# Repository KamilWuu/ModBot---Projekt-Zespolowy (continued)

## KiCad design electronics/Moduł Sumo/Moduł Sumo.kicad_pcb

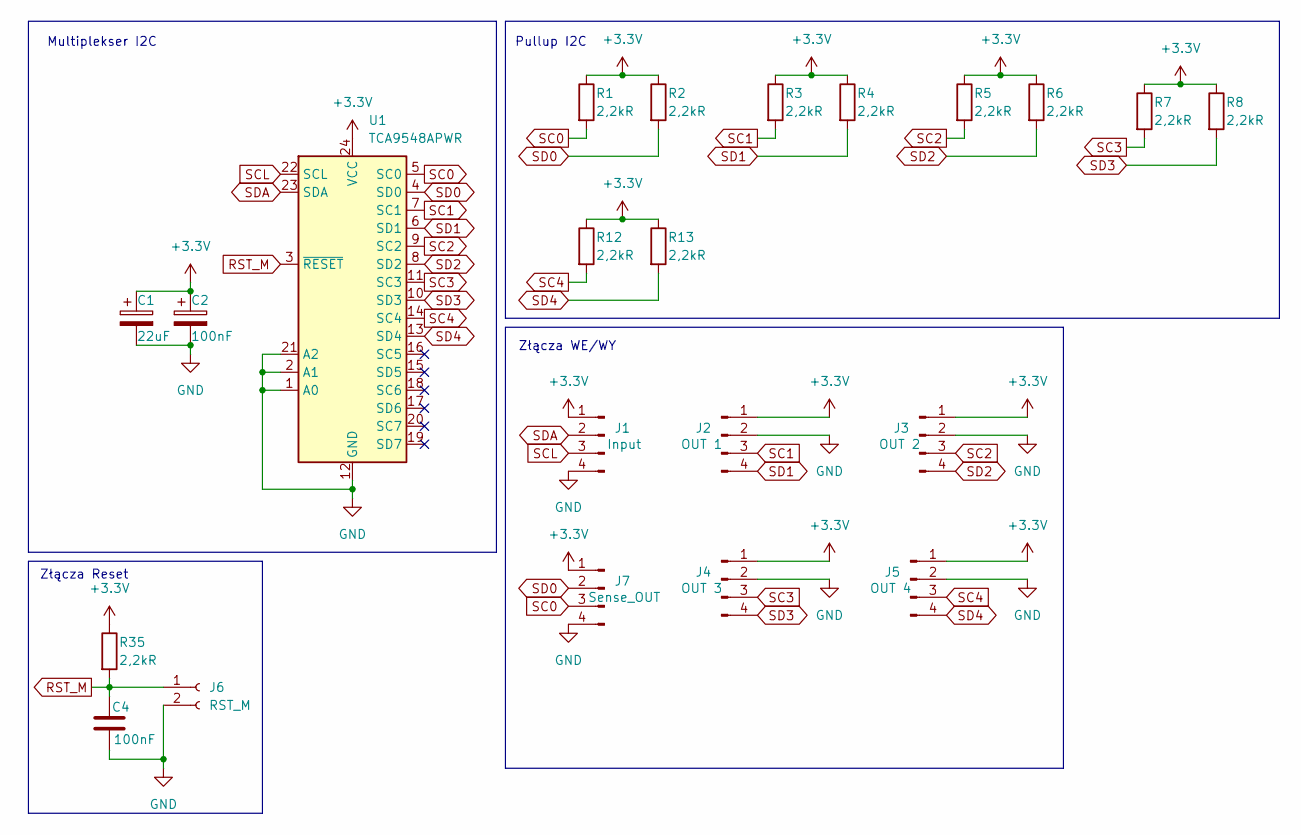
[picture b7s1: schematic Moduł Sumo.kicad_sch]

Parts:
C1: 22uF; C_0402_1005Metric_Pad0.74x0.62mm_HandSolder
C2, C4: 100nF; C_0402_1005Metric_Pad0.74x0.62mm_HandSolder
J1: Input; JST_EH_B4B-EH-A_1x04_P2.50mm_Vertical
J2: OUT 1; PinHeader_1x04_P2.54mm_Vertical
J3: OUT 2; PinHeader_1x04_P2.54mm_Vertical
J4: OUT 3; PinHeader_1x04_P2.54mm_Vertical
J5: OUT 4; PinHeader_1x04_P2.54mm_Vertical
J6: RST_M; PinSocket_1x02_P2.54mm_Vertical
J7: Sense_OUT; JST_EH_B4B-EH-A_1x04_P2.50mm_Vertical
R1, R2, R3, R4, R5, R6, R7, R8, R12, R13, R35: 2,2kR; R_0402_1005Metric_Pad0.72x0.64mm_HandSolder
U1: TCA9548APWR; TSSOP-24_4.4x7.8mm_P0.65mm

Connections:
+3.3V: C1.1, C2.1, J1.1, J2.1, J3.1, J4.1, J5.1, J7.1, R1.1, R2.1, R3.1, R4.1, R5.1, R6.1, R7.1, R8.1, R12.1, R13.1, R35.1, U1.24 (VCC)
GND: C1.2, C2.2, C4.2, J1.4, J2.2, J3.2, J4.2, J5.2, J6.2, J7.4, U1.1 (A0), U1.2 (A1), U1.12 (GND), U1.21 (A2)
RST_M: C4.1, J6.1, R35.2, U1.3 (~RESET)
SC0: J7.3, R1.2, U1.5 (SC0)
SC1: J2.3, R3.2, U1.7 (SC1)
SC2: J3.3, R5.2, U1.9 (SC2)
SC3: J4.3, R7.2, U1.11 (SC3)
SC4: J5.3, R12.2, U1.14 (SC4)
SCL: J1.3, U1.22 (SCL)
SD0: J7.2, R2.2, U1.4 (SD0)
SD1: J2.4, R4.2, U1.6 (SD1)
SD2: J3.4, R6.2, U1.8 (SD2)
SD3: J4.4, R8.2, U1.10 (SD3)
SD4: J5.4, R13.2, U1.13 (SD4)
SDA: J1.2, U1.23 (SDA)

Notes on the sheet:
Złącza Reset
Złącza WE/WY
Multiplekser I2C
Pullup I2C

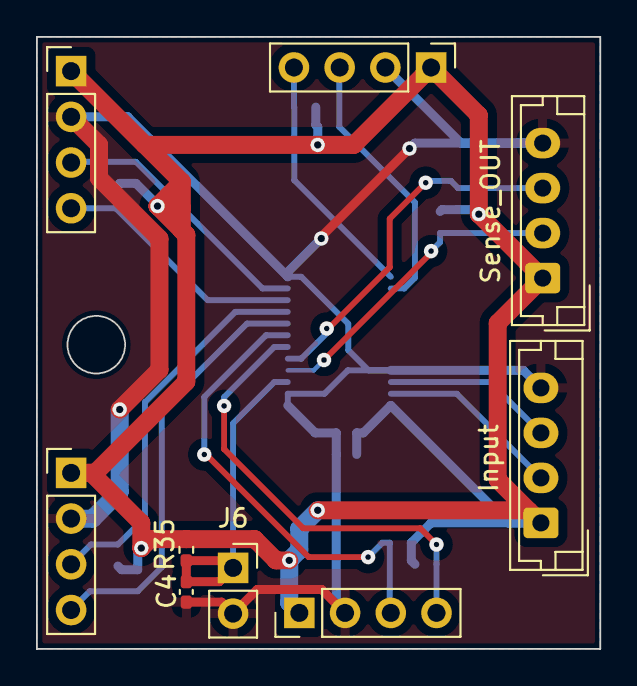
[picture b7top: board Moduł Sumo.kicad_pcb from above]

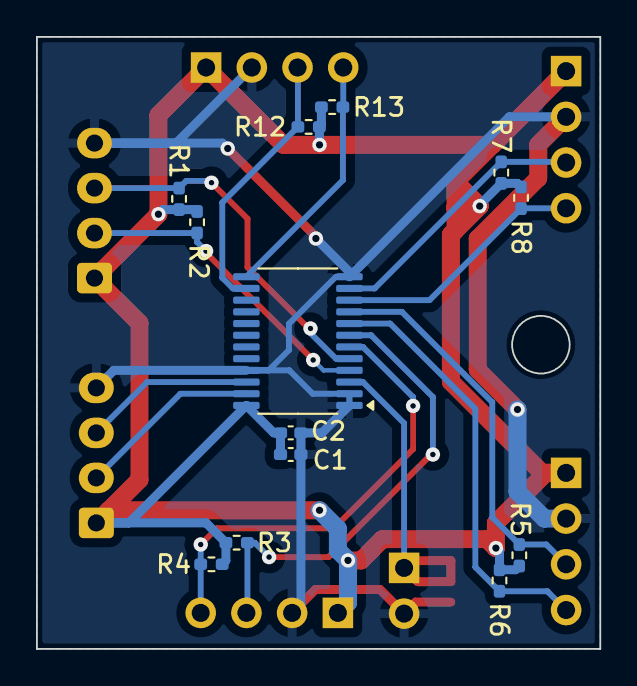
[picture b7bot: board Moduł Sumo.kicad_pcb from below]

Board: 2 copper layers, 31.3 x 34.0 mm, 22 parts (13 on the bottom side), 15 nets.

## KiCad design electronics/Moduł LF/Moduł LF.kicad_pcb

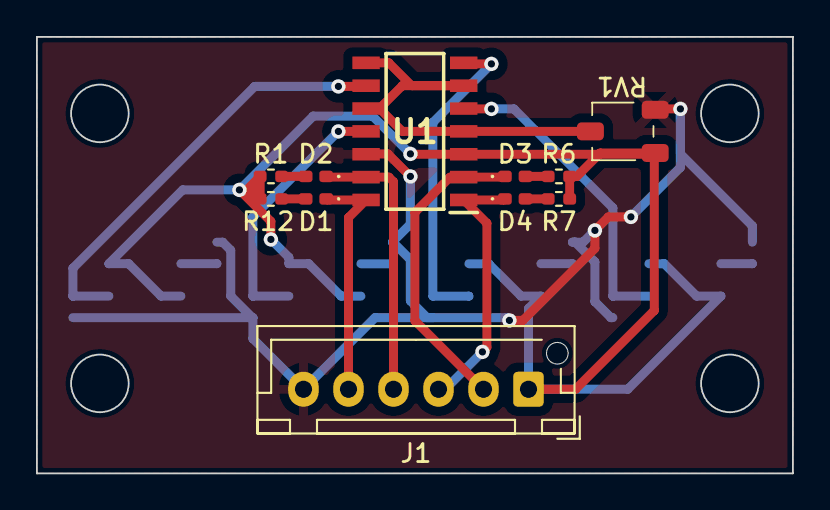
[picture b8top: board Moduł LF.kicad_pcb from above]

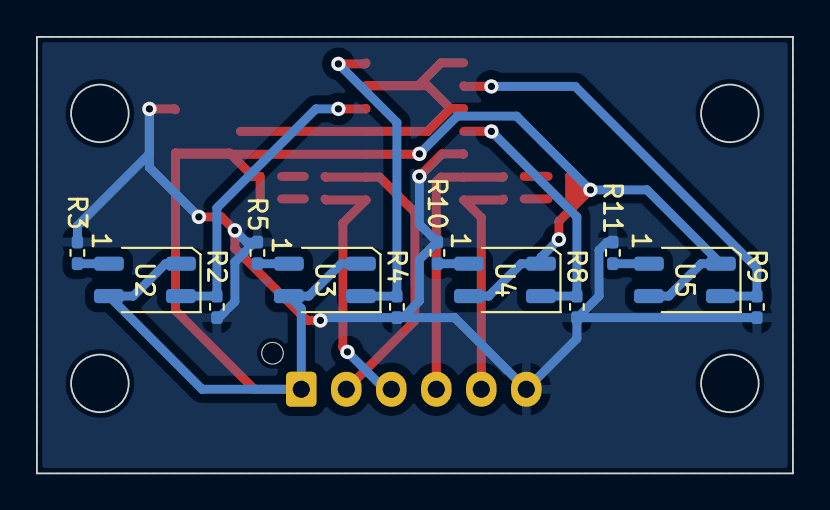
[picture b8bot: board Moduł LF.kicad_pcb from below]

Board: 2 copper layers, 42.0 x 24.2 mm, 23 parts (12 on the bottom side), 19 nets.

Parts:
D1, D2, D3, D4: LED; LED_0402_1005Metric_Pad0.77x0.64mm_HandSolder
J1: Conn_01x06_Socket; JST_XH_B6B-XH-AM_1x06_P2.50mm_Vertical
R1, R6, R7, R12: 330R; R_0402_1005Metric_Pad0.72x0.64mm_HandSolder
R2, R4, R8, R9: 22kR; R_0402_1005Metric_Pad0.72x0.64mm_HandSolder
R3, R5, R10, R11: 110R; R_0402_1005Metric_Pad0.72x0.64mm_HandSolder
RV1: R_Potentiometer; Potencjometr 3,2x3,4
U1: LM2901; SOIC127P600X175-14N
U2, U3, U4, U5: ITR8307-S17-TR8; Everlight_ITR1201SR10AR

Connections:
+3.3V: J1.1, R1.1, R6.1, R7.1, R12.1, RV1.1, U1.3 (V+), U2.2 (A), U2.3, U3.2 (A), U3.3, U4.2 (A), U4.3, U5.2 (A), U5.3
GND: J1.6, R2.2, R3.2, R4.2, R5.2, R8.2, R9.2, R10.2, R11.2, RV1.3, U1.12 (V-)
unnamed: D1.2 (A), R12.2
unnamed: D1.1 (K), J1.5, U1.14
unnamed: D2.2 (A), R1.2
unnamed: D2.1 (K), J1.4, U1.13
unnamed: D3.2 (A), R6.2
unnamed: D3.1 (K), J1.2, U1.2
unnamed: D4.2 (A), R7.2
unnamed: D4.1 (K), J1.3, U1.1
unnamed: R3.1, U2.1 (K)
unnamed: R5.1, U3.1 (K)
unnamed: R10.1, U4.1 (K)
unnamed: R11.1, U5.1 (K)
SIGNAL_IR_01: R2.1, U1.5 (+), U2.4
SIGNAL_IR_02: R4.1, U1.7 (+), U3.4
SIGNAL_IR_03: R8.1, U1.11 (+), U4.4
SIGNAL_IR_04: R9.1, U1.9 (+), U5.4
V_REF_IR: RV1.2, U1.4 (-), U1.6 (-), U1.8 (-), U1.10 (-)

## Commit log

2024-04-04 utworzono repozytorium projektu
2024-04-04 edycja readme
2024-04-04 pierwszy model 3D
2024-04-25 Utworzono pliki na schematy elektroniczne
2024-04-25 Dodano schematy sterownika silników, oraz modułu LF
2024-04-25 Dodano notatki dotyczące zmian
2024-04-26 Dalsze zmiany w elektronice
2024-04-26 Dodano schemat i footprint do ESP32
2024-04-26 Rozpoczęto pracę nad płytką minisumo
2024-04-27 wstepna mechanika
2024-04-27 Ukończenie modułu LF
2024-04-27 Poprawiono moduł Sumo i Dokończono moduł Hub LF
2024-04-28 test
2024-04-28 test2
2024-04-28 first mechanical project of main module
2024-04-28 drobne zmiany w mechanice
2024-04-28 dodano stl
2024-04-29 Utworzono modul sumo
2024-04-30 Ukończono moduł sumo
2024-04-30 Poprawiono płytkę ESP32
2024-05-01 Poprawiono płytki LF, zmieniono podejście do MiniSumo
2024-05-01 Zmiana koncepcji płytki od minisumo
2024-05-01 Dokończono alternatywną wersję płytki minisumo
2024-05-03 Wstępne zrobienie komunikacji, oraz zasilania
2024-05-04 Funkcjonalna płytka główna
2024-05-04 Ukończono płytkę główną
2024-05-05 Zmieniono wartości rezystorów i wygenerowano wstepną listę elementów do kupienia
2024-05-05 I have added footprint for joystick
2024-05-05 Dokonano panelizacji i wykonano pliki wierceń
2024-05-11 dodano plytke pilota
2024-05-12 rozpoczeto prace nad chwytakiem
2024-05-25 Dodano model 3D modulu LF i chwytaka
2024-05-26 poprawki w chwytaku i przygotowanie do druku
2024-06-21 I have added a code for ModBot
2024-06-22 poprawki w mechanice
